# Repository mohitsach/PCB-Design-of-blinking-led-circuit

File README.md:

# PCB Design of blinking led circuit in KiCad

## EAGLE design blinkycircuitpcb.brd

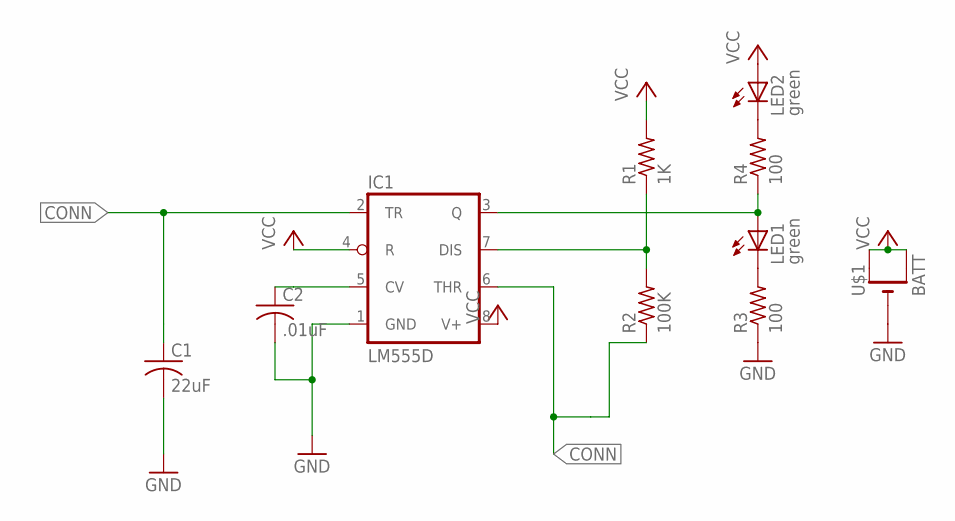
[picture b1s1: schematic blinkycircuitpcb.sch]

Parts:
C1: 22uF; C0805K
C2: .01uF; C0805K
IC1: LM555D; SO08
LED1, LED2: green; CHIPLED_0805
R1: 1K; R0805
R2: 100K; R0805
R3, R4: 100; R0805
U$1: BATT; CR1220-SMD

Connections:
CONN: C1.1, IC1.2 (TR), IC1.6 (THR), R2.1
GND: C1.2, C2.2, IC1.1 (GND), R3.1, U$1.-
unnamed: C2.1, IC1.5 (CV)
unnamed: LED1.C, R3.2
unnamed: LED2.C, R4.2
unnamed: IC1.3 (Q), LED1.A, R4.1
unnamed: IC1.7 (DIS), R1.1, R2.2
VCC: IC1.4 (R), IC1.8 (V+), LED2.A, R1.2, U$1.+$1 (+), U$1.+$2 (+1)

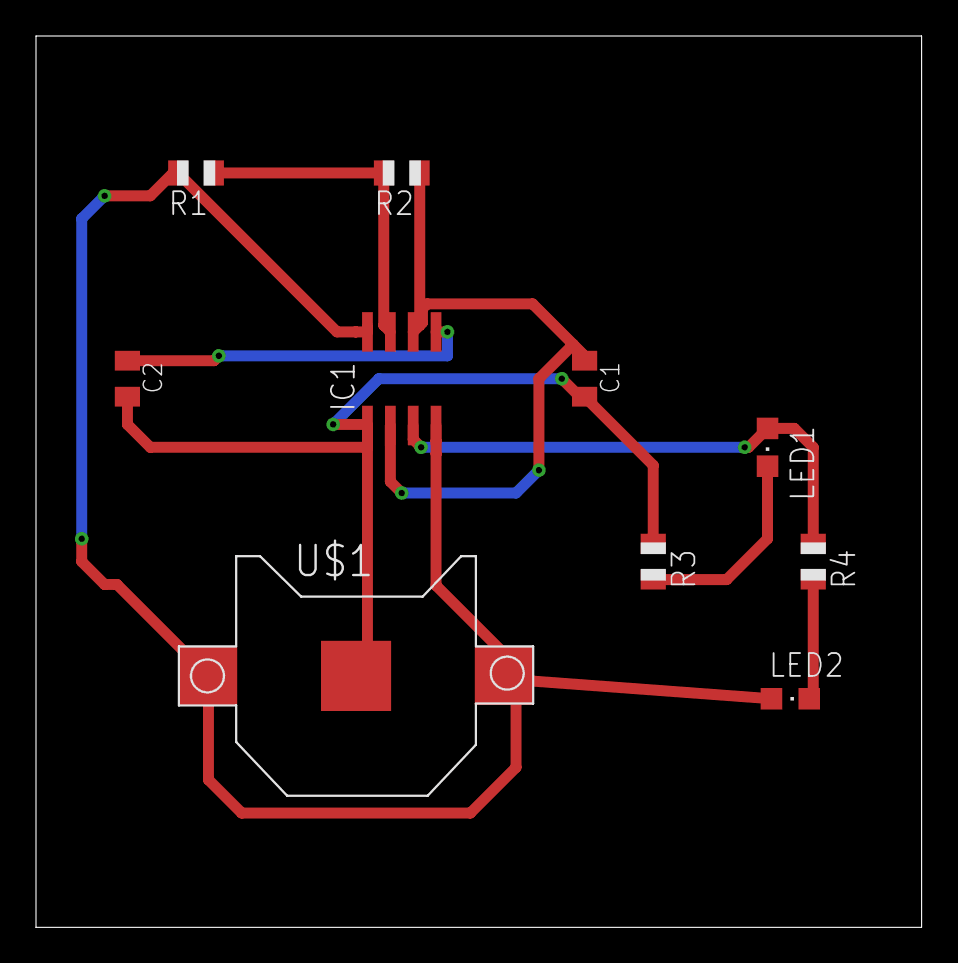
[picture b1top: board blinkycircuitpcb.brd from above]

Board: 2 copper layers, 49.2 x 49.5 mm, 10 parts (0 on the bottom side), 8 nets.
